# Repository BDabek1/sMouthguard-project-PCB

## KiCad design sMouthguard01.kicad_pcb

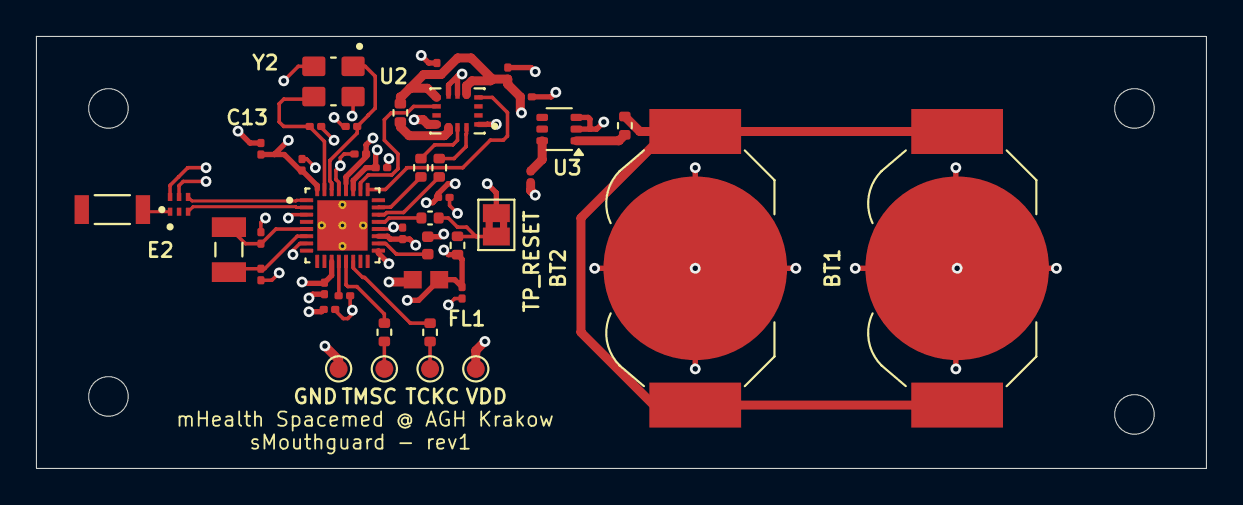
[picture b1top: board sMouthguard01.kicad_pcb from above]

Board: 4 copper layers, 65.0 x 24.0 mm, 42 parts (0 on the bottom side), 29 nets.

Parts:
BT1, BT2: CR1632; BatteryHolder_LINX_BAT-HLD-012-SMT
C1, C13: DNM; C_0201_0603Metric
C2, C6, C9, C11, C12: 100nF; C_0201_0603Metric
C7: 10uF-ceramic; C_0201_0603Metric
C8, C10: 10uF; C_0201_0603Metric
C14: 10nF; C_0201_0603Metric
C15: 100nF; C_0402_1005Metric
C16: 0.1uF; C_0201_0603Metric
C17: 1uF; C_0201_0603Metric
C18: 2.2uF; C_0201_0603Metric
C19, C20: 10pF; C_0201_0603Metric
C21, C22: 12pF; C_0201_0603Metric
E2: 2450AT18A0100001E; XCVR_2450AT18A0100001E
FL1: BLM18HE152SN1D; BEADC1608X95N
GND: GND; TestPoint_Pad_D1.0mm
L1: 10 uH; L_0402_1005Metric
R1, R3, R7, R8: 2.2kOhm; R_0402_1005Metric
R2: 10kOhm; R_0402_1005Metric
R4: 0Ohm; R_0402_1005Metric
R6: 1 Ohm; R_0402_1005Metric
TCKC: JTAG_TCKC; TestPoint_Pad_D1.0mm
TMSC: JTAG_TMSC; TestPoint_Pad_D1.0mm
TP_RESET: TP; SolderJumper-2_P1.3mm_Bridged2Bar_Pad1.0x1.5mm
U2: ICM-45686; IC_ICM-45686
U3: LM66100DCK; SOT-363_SC-70-6
U4: CC2640R2FRSMR; QFN40P400X400X100-33N
VDD: VBAT; TestPoint_Pad_D1.0mm
Y1: ABS07-32.768KHZ-7-T; XTAL_ABS07-32.768KHZ-7-T
Y2: TSX-322524.0000MF15X-AC3; OSCCC320X250X60
Z2: 2450BM14G0011T; BALUN_2450BM14G0011T

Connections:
/DCDC_SW: L1.1, U4.18 (DCDC_SW)
/I2C_N: R7.2, U4.23 (DIO_6)
/I2C_P: R8.2, U4.22 (DIO_5)
/I2C_SCL: R7.1, U2.13 (AP_SCL)
/I2C_SDA: R8.1, U2.14 (AP_SDA)
/INT1: U2.4 (INT1), U4.25 (DIO_8)
/INT2: U2.9 (INT2/FSYNC/CLKIN), U4.26 (DIO_9)
/JTAG_TCKC: R1.1, U4.14 (JTAG_TCKC)
/JTAG_TMSC: R3.1, U4.13 (JTAG_TMSC)
/RF_N: U4.2 (RF_N), Z2.3 (BALANCED_PORT)
/RF_P: U4.1 (RF_P), Z2.4 (BALANCED_PORT)
/VDDR: C10.1, C11.1, C12.1, C13.1, L1.2, U4.28 (VDDR), U4.32 (VDDR_RF)
/VDDS: C1.1, C2.1, C6.1, C8.1, C9.1, FL1.2, R2.1, U4.11 (VDDS2), U4.19 (VDDS_DCDC), U4.27 (VDDS)
GND: BT1.2 (-), BT2.2 (-), C1.2, C2.2, C6.2, C8.2, C9.2, C10.2, C11.2, C12.2, C13.2, C14.2, C16.2, C17.1, C18.2, C19.1, C20.1, C21.1, C22.2, GND.1, TP_RESET.1, U2.1 (AP_AD0), U2.6 (GND), U2.7 (RESV), U2.11 (RESV/AUX1_SDO), U3.2 (GND), U3.3 (~CE), U4.3 (VSS), U4.7 (VSS), U4.17 (VSS), U4.20 (VSS), U4.29 (VSS), U4.33 (EXP), U4.33_1 (EXP), U4.33_2 (EXP), U4.33_3 (EXP), U4.33_4 (EXP), U4.33_5 (EXP), Y2.2, Y2.4, Z2.5 (GND), Z2.6 (GND)
unnamed: BT1.1 (+), BT2.1 (+), R6.2
unnamed: C15.2, R2.2, TP_RESET.2
unnamed: R1.2, TCKC.1
unnamed: R3.2, TMSC.1
unnamed: R4.1, U2.12 (AP_CS)
unnamed: R6.1, U3.1 (VIN)
unnamed: C7.2, U3.6 (VOUT)
unnamed: C17.2, U4.12 (DCOUPL)
unnamed: C21.2, U4.30 (X24M_N), Y2.1
unnamed: C22.1, U4.31 (X24M_P), Y2.3
unnamed: C19.2, U4.5 (X32K_Q1), Y1.2
unnamed: C20.2, U4.6 (X32K_Q2), Y1.1
unnamed: C15.1, U4.21 (~RESET_N)
unnamed: E2.1, Z2.1 (UNBALANCED_PORT)
VDD_EB: C7.1, C14.1, C16.1, C18.1, FL1.1, R4.2, U2.5 (VDDIO), U2.8 (VDD), VDD.1

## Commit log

2026-04-26 Initial commit with ICM-45686
2026-04-26 Create README.md with graphics from KiCAD
